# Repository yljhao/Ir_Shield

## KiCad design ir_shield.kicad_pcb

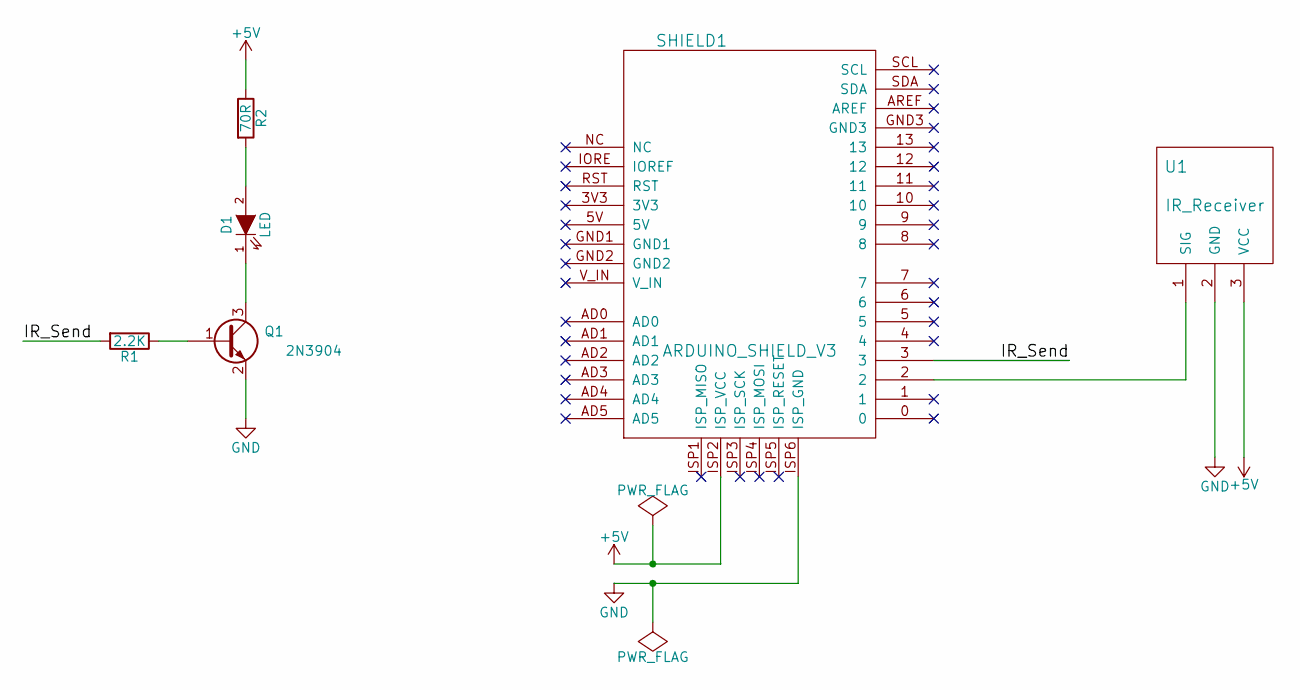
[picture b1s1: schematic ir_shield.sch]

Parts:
D1: LED; LED-5MM
Q1: 2N3904; SOT-23
R1: 2.2K; R4
R2: 70R; R4
SHIELD1: ARDUINO_SHIELD_V3; ARDUINO_SHIELD_V3_040pins
U1: IR_Receiver; Pin_Header_Straight_1x03

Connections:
+5V: R2.1, SHIELD1.ISP2 (ISP_VCC), U1.3 (VCC)
/IR_Send: R1.2, SHIELD1.3
GND: Q1.2 (E), SHIELD1.ISP6 (ISP_GND), U1.2 (GND)
unnamed: D1.1 (K), Q1.3 (C)
unnamed: D1.2 (A), R2.2
unnamed: Q1.1 (B), R1.1
unnamed: SHIELD1.2, U1.1 (SIG)

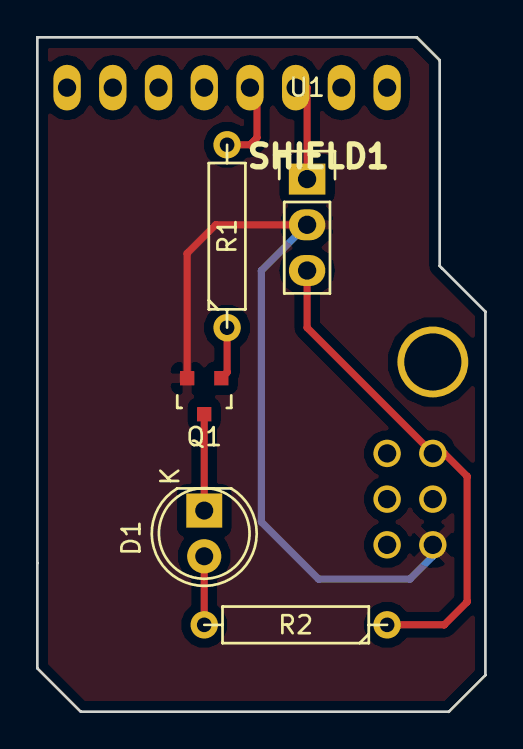
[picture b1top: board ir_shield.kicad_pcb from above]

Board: 2 copper layers, 24.9 x 37.5 mm, 6 parts (0 on the bottom side), 7 nets.

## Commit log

2016-06-01 First Commit.
2016-06-03 Re-mod PCB into smaller size.
